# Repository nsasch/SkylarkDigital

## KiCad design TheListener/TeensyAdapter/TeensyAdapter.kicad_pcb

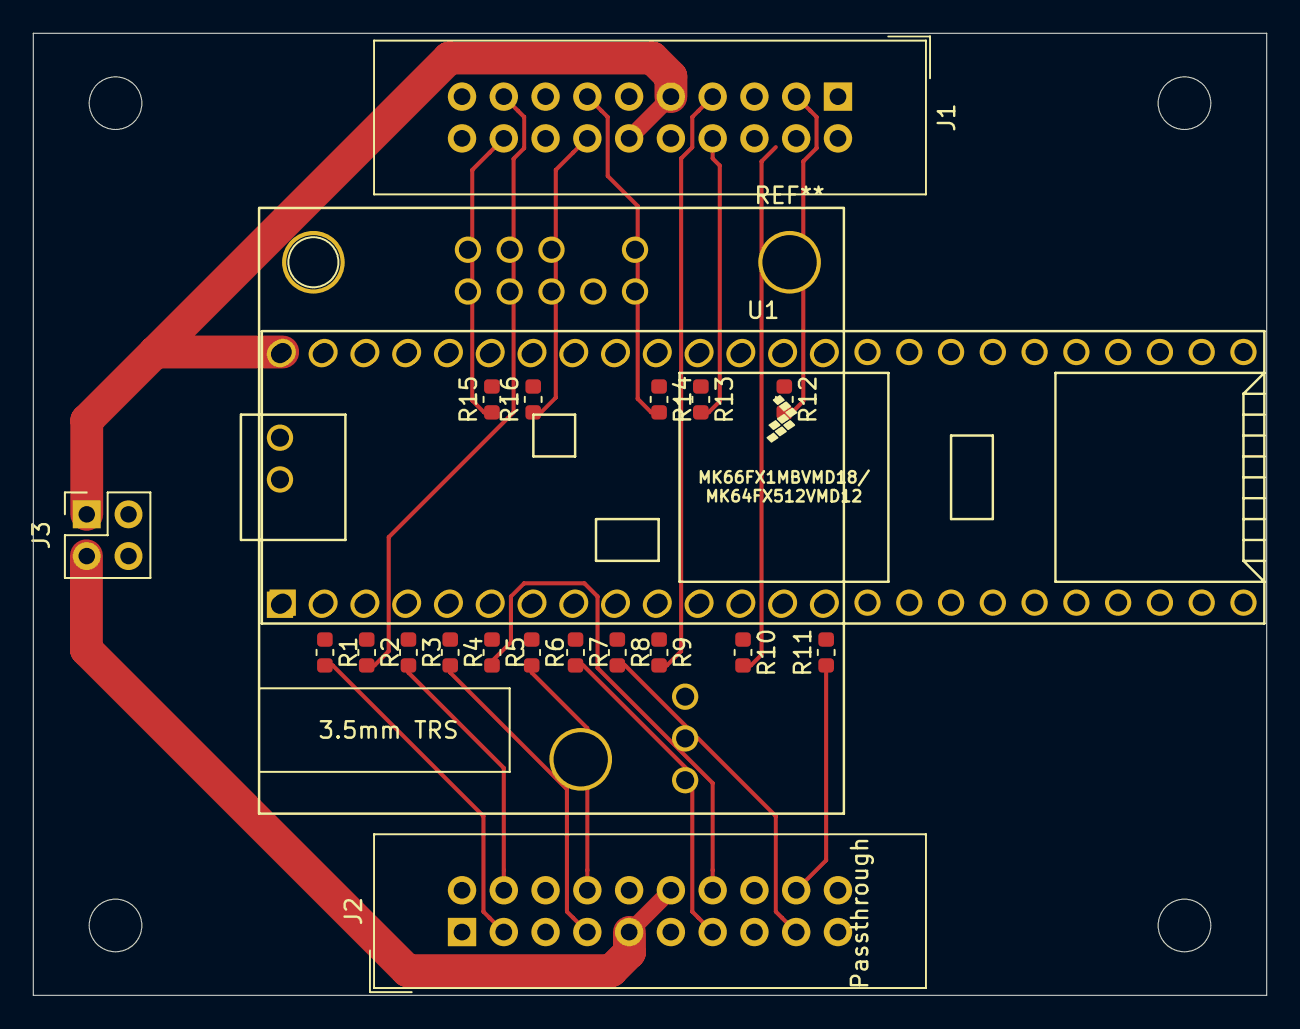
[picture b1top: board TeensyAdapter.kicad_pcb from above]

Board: 2 copper layers, 75.0 x 58.5 mm, 24 parts (0 on the bottom side), 34 nets.

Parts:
H1, H2, H3, H4: MountingHole; MountingHole_3.2mm_M3
J1, J2: Conn_02x10_Odd_Even; IDC-Header_2x10_P2.54mm_Vertical
J3: Conn_02x02_Odd_Even; PinSocket_2x02_P2.54mm_Vertical
R1, R2, R3, R4, R5, R6, R7, R8, R9, R10, R11, R12, R13, R14, R15, R16: 100; R_0603_1608Metric
U1: Teensy3.5; Teensy35_36_NoMiddlePins

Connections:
+5V: J1.9, J1.12, J2.9, J2.12, J3.1, J3.2, U1.53
GND: J1.1, J1.2, J1.5, J1.6, J1.10, J1.11, J1.15, J1.16, J1.19, J1.20, J2.1, J2.2, J2.5, J2.6, J2.10, J2.11, J2.15, J2.16, J2.19, J2.20, J3.3, J3.4, U1.1
unnamed: R1.1, U1.2
unnamed: R2.1, U1.3
unnamed: R3.1, U1.4
unnamed: R4.1, U1.5
unnamed: R5.1, U1.6
unnamed: R6.1, U1.7
unnamed: R7.1, U1.8
unnamed: R8.1, U1.9
unnamed: R9.1, U1.10
unnamed: R10.1, U1.12
unnamed: R11.2, U1.14
unnamed: R12.1, U1.41
unnamed: R13.1, U1.43
unnamed: R14.1, U1.44
unnamed: R15.2, U1.48
unnamed: R16.2, U1.47
R_1: J2.18, R11.1
R_2: J2.14, R5.2
R_3: J2.7, R4.2
R_4: J2.3, R1.2
R_5: J1.4, R10.2
R_6: J1.8, R13.2
R_7: J1.13, R14.2
R_8: J1.17, R2.2
T_1: J2.17, R8.2
T_2: J2.13, R7.2
T_3: J2.8, R6.2
T_4: J2.4, R3.2
T_5: J1.3, R12.2
T_6: J1.7, R9.2
T_7: J1.14, R16.1
T_8: J1.18, R15.1

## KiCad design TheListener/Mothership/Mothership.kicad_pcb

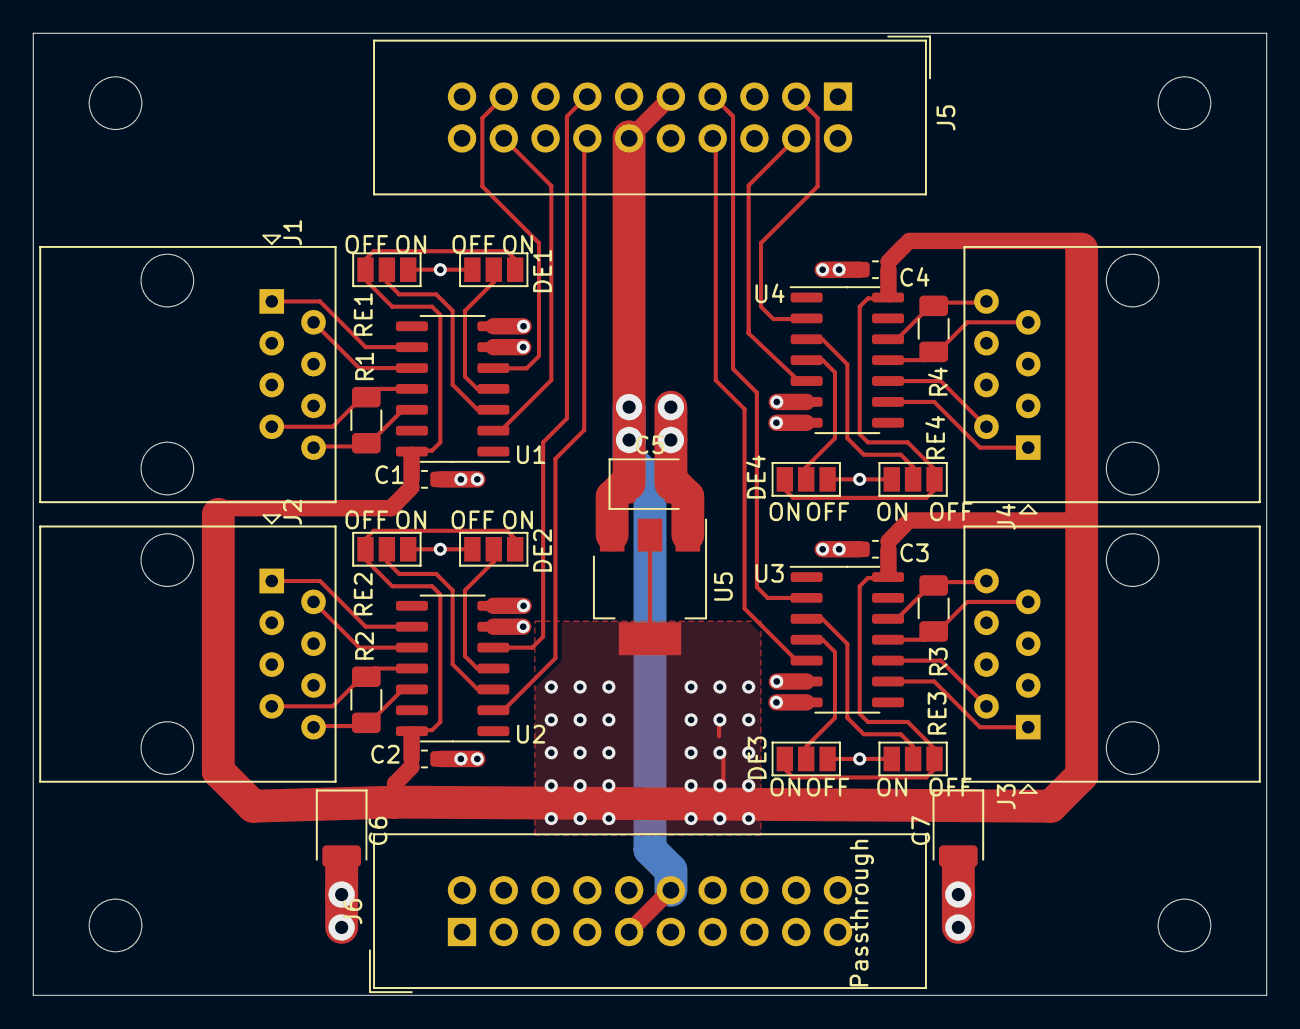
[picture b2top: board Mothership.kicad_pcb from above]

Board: 2 copper layers, 75.0 x 58.5 mm, 34 parts (0 on the bottom side), 35 nets.

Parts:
C1, C2, C3, C4: 100nF; C_0603_1608Metric
C5: 22uF; CP_EIA-3528-21_Kemet-B
C6, C7: 10uF; CP_EIA-3528-21_Kemet-B
DE1, DE2, DE3, DE4: SW_SPDT; SolderJumper-3_P1.3mm_Open_Pad1.0x1.5mm_EnableLabels
H1, H2, H3, H4: MountingHole; MountingHole_3.2mm_M3
J1, J2, J3, J4: RJ45; RJ45_Amphenol_54602-x08_Horizontal
J5, J6: Conn_02x10_Odd_Even; IDC-Header_2x10_P2.54mm_Vertical
R1, R2, R3, R4: 100; R_1206_3216Metric
RE1, RE2, RE3, RE4: SW_SPDT; SolderJumper-3_P1.3mm_Open_Pad1.0x1.5mm_EnableLabels
U1, U2, U3, U4: SP3491; SOIC-14_3.9x8.7mm_P1.27mm
U5: AMS1117-3.3; SOT-223-3_TabPin2

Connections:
+3V3: C1.2, C2.2, C3.2, C4.2, C6.1, C7.1, DE1.1, DE2.1, DE3.1, DE4.1, RE1.3, RE2.3, RE3.3, RE4.3, U1.14, U2.14, U3.14, U4.14, U5.2
+5V: C5.1, J5.9, J5.12, J6.9, J6.12, U5.3
GND: C1.1, C2.1, C3.1, C4.1, C5.2, C6.2, C7.2, DE1.3, DE2.3, DE3.3, DE4.3, J1.3, J1.4, J1.5, J1.6, J2.3, J2.4, J2.5, J2.6, J3.3, J3.4, J3.5, J3.6, J4.3, J4.4, J4.5, J4.6, J5.1, J5.2, J5.5, J5.6, J5.10, J5.11, J5.15, J5.16, J5.19, J5.20, J6.1, J6.2, J6.5, J6.6, J6.10, J6.11, J6.15, J6.16, J6.19, J6.20, RE1.1, RE2.1, RE3.1, RE4.1, U1.6, U1.7, U2.6, U2.7, U3.6, U3.7, U4.6, U4.7, U5.1
unnamed: DE1.2, U1.4
unnamed: DE2.2, U2.4
unnamed: DE3.2, U3.4
unnamed: DE4.2, U4.4
unnamed: J1.1, U1.9
unnamed: J1.2, U1.10
unnamed: J1.7, R1.2, U1.11
unnamed: J1.8, R1.1, U1.12
unnamed: J2.1, U2.9
unnamed: J2.2, U2.10
unnamed: J2.7, R2.2, U2.11
unnamed: J2.8, R2.1, U2.12
unnamed: J3.1, U3.9
unnamed: J3.2, U3.10
unnamed: J3.7, R3.2, U3.11
unnamed: J3.8, R3.1, U3.12
unnamed: J4.1, U4.9
unnamed: J4.2, U4.10
unnamed: J4.7, R4.2, U4.11
unnamed: J4.8, R4.1, U4.12
unnamed: RE1.2, U1.3
unnamed: RE2.2, U2.3
unnamed: RE3.2, U3.3
unnamed: RE4.2, U4.3
R_1: J5.18, U1.2
R_2: J5.14, U2.2
R_3: J5.7, U3.2
R_4: J5.3, U4.2
T_1: J5.17, U1.5
T_2: J5.13, U2.5
T_3: J5.8, U3.5
T_4: J5.4, U4.5

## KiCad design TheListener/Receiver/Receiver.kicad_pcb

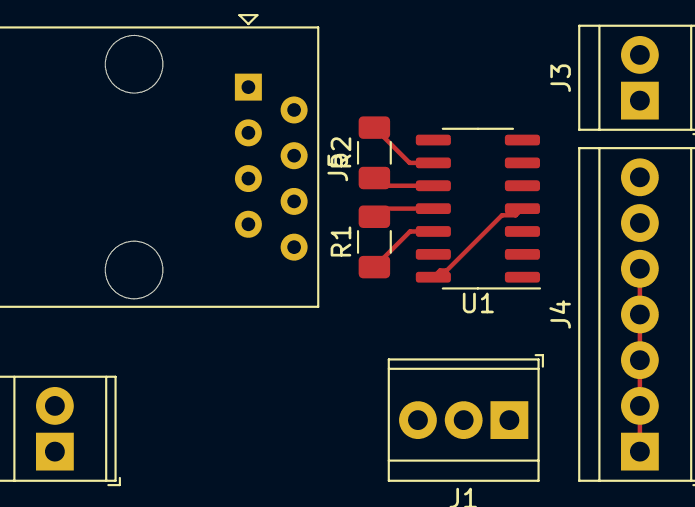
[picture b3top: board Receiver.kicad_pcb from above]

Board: 2 copper layers, 8 parts (0 on the bottom side), 9 nets.

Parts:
J1: Conn_01x03_Female; TerminalBlock_TE_282834-3_1x03_P2.54mm_Horizontal
J2, J3: Conn_01x02_Female; TerminalBlock_TE_282834-2_1x02_P2.54mm_Horizontal
J4: Conn_01x07_Male; TerminalBlock_TE_282834-7_1x07_P2.54mm_Horizontal
J5: 8P8C; RJ45_Amphenol_54602-x08_Horizontal
R1, R2: R; R_1206_3216Metric
U1: SP491E; SOIC-14_3.9x8.7mm_P1.27mm

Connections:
+5V: J1.1, J4.1, J4.2, J4.3, J4.4, J4.5, U1.4, U1.14
+24V: J1.2, J2.2
/BTN: J3.1, U1.5
/BTN_A: J5.8, R2.2, U1.9
/BTN_B: J5.7, R2.1, U1.10
/DATA: J4.6, U1.2
/DATA_A: J5.1, R1.1, U1.12
/DATA_B: J5.2, R1.2, U1.11
GND: J1.3, J2.1, J3.2, J4.7, J5.3, J5.4, J5.5, J5.6, U1.3, U1.6, U1.7

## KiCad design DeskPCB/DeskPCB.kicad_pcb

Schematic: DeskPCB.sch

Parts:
C1, C2: C; C_Disc_D3.0mm_W2.0mm_P2.50mm
J1, J2: 8P8C; RJ45_Amphenol_54602-x08_Horizontal
J3, J5: USB_B_Micro; USB_Micro_B_Female_10118193-0001LF
J4: Conn_01x05_Female; TerminalBlock_Phoenix_PTSM-0,5-5-2.5-H-THR_1x05_P2.50mm_Hor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
R1, R2, R3, R4, R5: R; R_Axial_DIN0309_L9.0mm_D3.2mm_P2.54mm_Vertical
U1: 74125; DIP-14_W7.62mm_Socket
U2: WeMos_D1_mini; WEMOS_D1_mini_light

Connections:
+3V3: R1.1, R2.1, R3.1, U2.8 (3V3)
+5V: J3.1, J4.5
DWN_BTN: J1.8, U2.14 (SCL/D1)
DWN_DESK: J2.8, U1.3 (O)
DWN_MCU: R1.2, U1.1 (EN), U2.5 (MISO/D6)
GND: C1.2, C2.1, J1.3, J2.3, J3.5, J4.1, J5.5, U1.2 (D), U1.5 (D), U1.7 (GND), U1.12 (D), U2.10 (GND)
LEDS_MCU: R5.2, U1.9 (D)
LEDS_OUT: J4.2, R4.2
N_EN_LIGHTS: R2.2, U1.10 (EN), U2.4 (SCK/D5)
unnamed: R4.1, U1.8 (O)
unnamed: R5.1, U2.11 (D4)
UP_BTN: J1.7, U2.13 (SDA/D2)
UP_DESK: J2.7, U1.6 (O)
UP_MCU: R3.2, U1.4 (EN), U2.6 (MOSI/D7)
VCC: C1.1, C2.2, J4.3, J5.1, U1.13 (EN), U1.14 (VCC), U2.9 (5V)

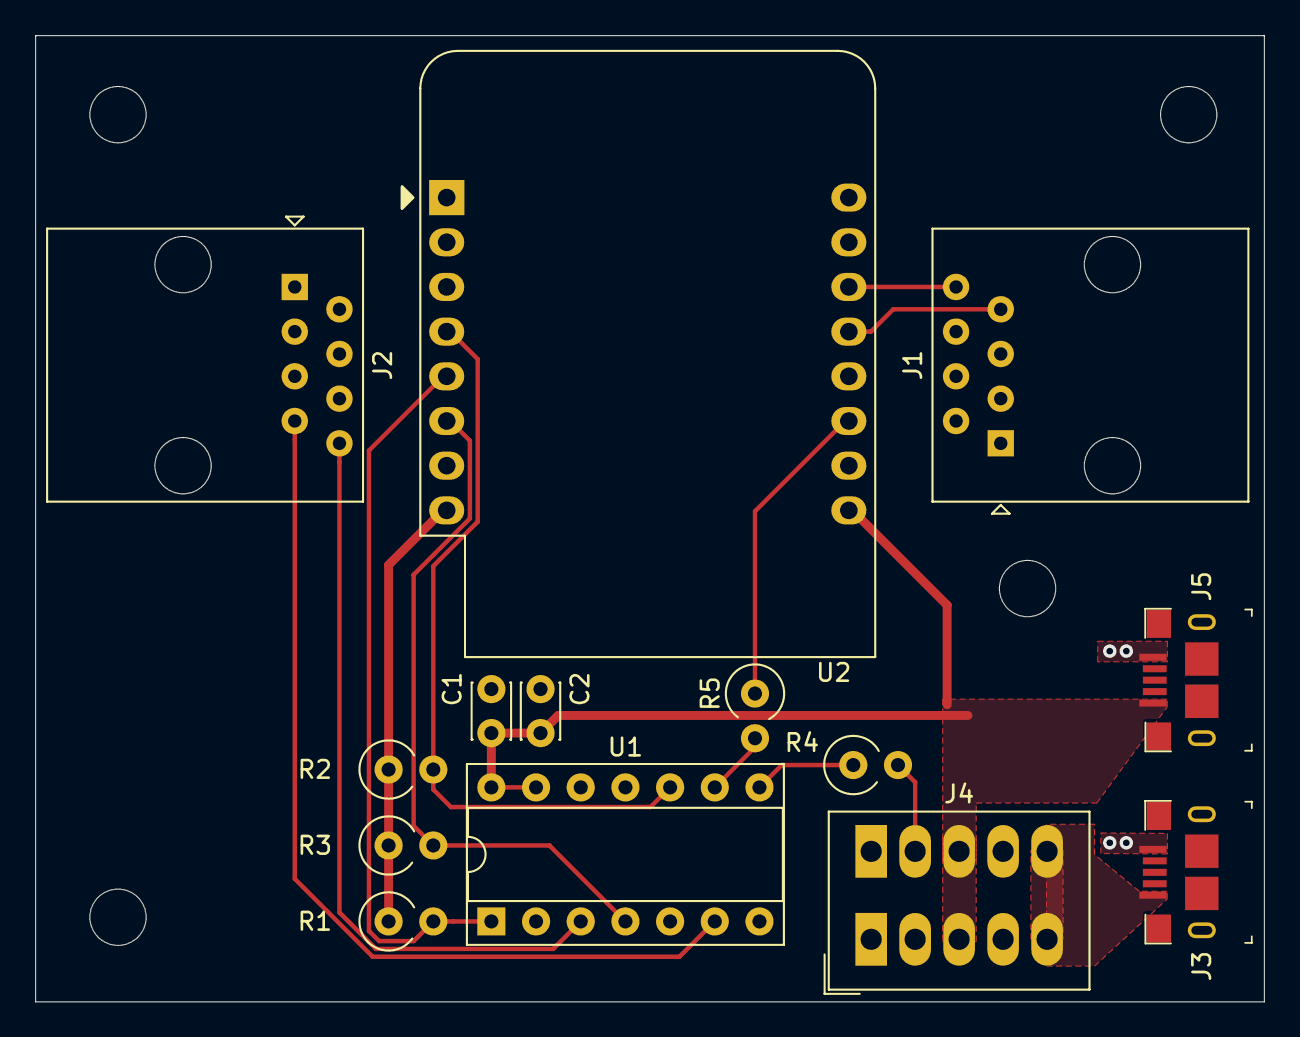
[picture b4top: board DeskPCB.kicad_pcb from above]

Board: 2 copper layers, 69.8 x 54.9 mm, 17 parts (0 on the bottom side), 15 nets.

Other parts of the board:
 : MountingHole_3.2mm_M3
 #2,  #3: MountingHole_3.2mm_M3

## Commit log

2019-12-25 updates fixes
2019-12-26 mothership progress
2019-12-26 moving to hierarchical
2019-12-26 minor layout updates
2019-12-27 better
2019-12-27 moar
2019-12-27 layout for one port
2019-12-27 updates to layout
2019-12-28 almost
2019-12-28 all except signals; needs refinement of power
2019-12-30 updates and plots
2019-12-30 updated plots and drills
2020-01-11 receiver, updates, desk bom
2020-01-13 final
2020-01-13 adapter
2020-01-14 working
2020-01-15 adding shield drawing
2020-01-17 updates to add power correctly
2020-01-17 audio shield etc
2020-01-22 four-port wip
2020-01-22 narrower
2020-01-22 updates, mothership finished
2020-01-26 esp32 testing
2020-01-26 esp32 time server
2020-01-29 time syncing
2020-02-01 time working
2020-02-02 new-sampling
